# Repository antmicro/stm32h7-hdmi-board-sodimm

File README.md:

# SODIMM for STM32H7 HDMI Board

Copyright (c) 2026 [Antmicro](https://www.antmicro.com)

## Overview

This project includes PCB design files for a custom SDRAM memory module in SO-DIMM form factor. 
This module is compatible with [STM32H7 HDMI Board](https://github.com/antmicro/stm32h7-hdmi-board) developed by Antmicro. 
It provides 512 MB of SDRAM memory supporting a maximum memory clock frequency of 200 MHz, and exposes a 32-bit data bus for full compatibility with the STM32H747 FMC (Flexible Memory Controller) used in the STM32H7 HDMI Board design. 
The board design follows the JEDEC 144-pin SODIMM pin assignment with only half of the data bus implemented (32 bits).
It also features an EEPROM memory chip for Serial Presence Detect.
The board dimensions comply with the MO-190-C SODIMM Mechanical Specifications.
The PCB design files were prepared in KiCad 10.x.

## Key features

* 512 MB of SDRAM memory
* 144 Pin SODIMM PCB edge connector
* 2Rx8 (32 data bus) memory organization
* 8 x ISSI IS42S86400F-7TL SDRAM devices with a maximum clock frequency of 200MHz
* JEDEC 144-pin SODIMM pin-assignment with only half of the data bus implemented (DQ[0..31])
* Board outline compliant with the MO-190-C SODIMM Mechanical Specifications
* Compatible with STM32H747 FMC
* 67.6 x 31.75 mm (2.66 x 1.25 inch) PCB outline

## Project structure

The main directory contains KiCad PCB project files, the LICENSE, and this README, and the img directory contains graphics for this README.

## Licensing

This project is published under the [Apache-2.0](LICENSE) license.

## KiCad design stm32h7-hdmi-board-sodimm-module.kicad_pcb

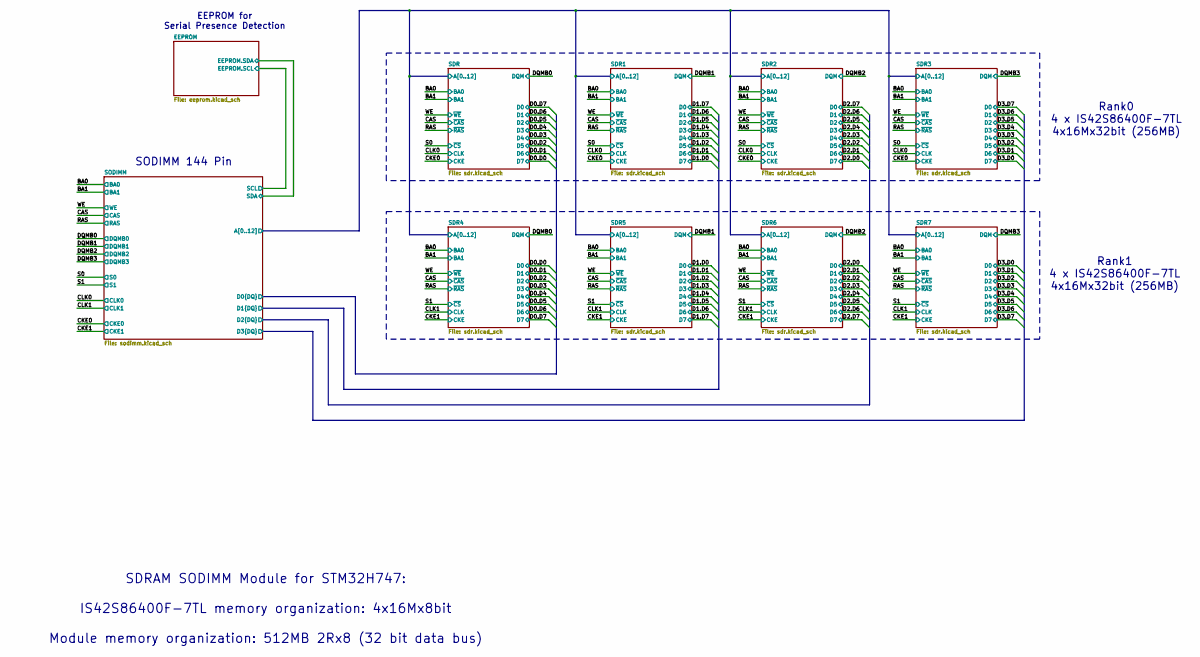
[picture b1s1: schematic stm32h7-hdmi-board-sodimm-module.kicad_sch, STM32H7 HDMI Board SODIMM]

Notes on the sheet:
Rank0 4 x IS42S86400F-7TL 4x16Mx32bit (256MB)
Rank1 4 x IS42S86400F-7TL 4x16Mx32bit (256MB)
SDRAM SODIMM Module for STM32H747: IS42S86400F-7TL memory organization: 4x16Mx8bit Module memory organization: 512MB 2Rx8 (32 bit data bus)
SODIMM 144 Pin
EEPROM for Serial Presence Detection

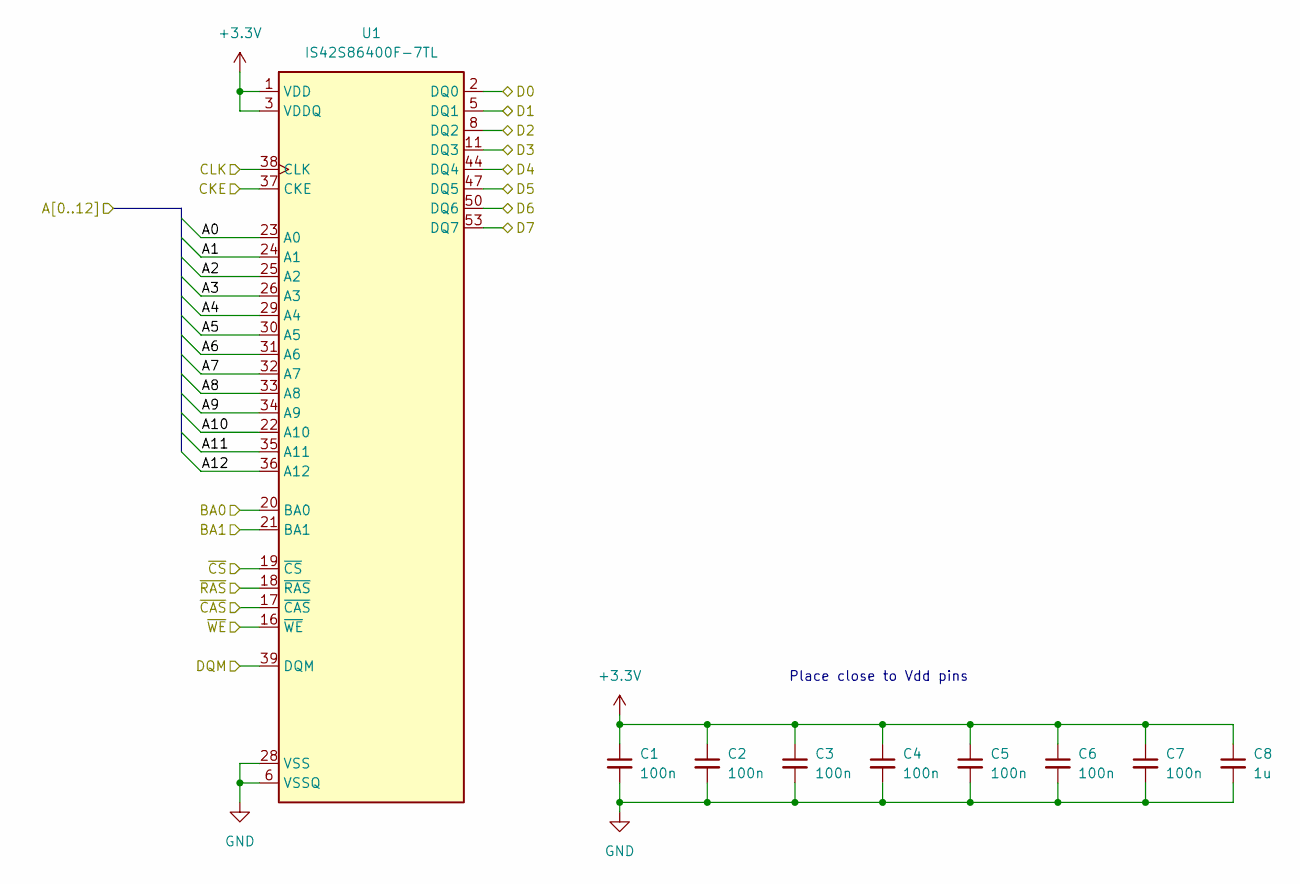
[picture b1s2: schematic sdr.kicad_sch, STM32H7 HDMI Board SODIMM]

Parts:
C1, C2, C3, C4, C5, C6, C7: C_100n_0402; C_0402_1005Metric; Voltage 50V; MPN GRM155R61H104KE14D
C8: C_1u_0402; C_0402_1005Metric; MPN C1005X6S1A105K050BC
U1: IS42S86400F-7TL; TSOP-II-54_22.2x10.16mm_P0.8mm; MPN IS42S86400F-7TL

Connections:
+3.3V: C1.1, C2.1, C3.1, C4.1, C5.1, C6.1, C7.1, C8.1, U1.1 (VDD), U1.3 (VDDQ), U1.9 (VDDQ), U1.14 (VDD), U1.27 (VDD), U1.43 (VDDQ), U1.49 (VDDQ); also elsewhere on the board
/BA0: U1.20 (BA0); also elsewhere on the board
/BA1: U1.21 (BA1); also elsewhere on the board
/CAS: U1.17 (~CAS); also elsewhere on the board
/CKE0: U1.37 (CKE); also elsewhere on the board
/CLK0: U1.38 (CLK); also elsewhere on the board
/DQMB0: U1.39 (DQM); also elsewhere on the board
/RAS: U1.18 (~RAS); also elsewhere on the board
/S0: U1.19 (~CS); also elsewhere on the board
/SDR/A0: U1.23 (A0); also elsewhere on the board
/SDR/A1: U1.24 (A1); also elsewhere on the board
/SDR/A2: U1.25 (A2); also elsewhere on the board
/SDR/A3: U1.26 (A3); also elsewhere on the board
/SDR/A4: U1.29 (A4); also elsewhere on the board
/SDR/A5: U1.30 (A5); also elsewhere on the board
/SDR/A6: U1.31 (A6); also elsewhere on the board
/SDR/A7: U1.32 (A7); also elsewhere on the board
/SDR/A8: U1.33 (A8); also elsewhere on the board
/SDR/A9: U1.34 (A9); also elsewhere on the board
/SDR/A10: U1.22 (A10); also elsewhere on the board
/SDR/A11: U1.35 (A11); also elsewhere on the board
/SDR/A12: U1.36 (A12); also elsewhere on the board
/SODIMM/D0.D0: U1.53 (DQ7); also elsewhere on the board
/SODIMM/D0.D1: U1.50 (DQ6); also elsewhere on the board
/SODIMM/D0.D2: U1.47 (DQ5); also elsewhere on the board
/SODIMM/D0.D3: U1.44 (DQ4); also elsewhere on the board
/SODIMM/D0.D4: U1.11 (DQ3); also elsewhere on the board
/SODIMM/D0.D5: U1.8 (DQ2); also elsewhere on the board
/SODIMM/D0.D6: U1.5 (DQ1); also elsewhere on the board
/SODIMM/D0.D7: U1.2 (DQ0); also elsewhere on the board
/WE: U1.16 (~WE); also elsewhere on the board
GND: C1.2, C2.2, C3.2, C4.2, C5.2, C6.2, C7.2, C8.2, U1.6 (VSSQ), U1.12 (VSSQ), U1.28 (VSS), U1.41 (VSS), U1.46 (VSSQ), U1.52 (VSSQ), U1.54 (VSS); also elsewhere on the board

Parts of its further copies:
C9, C10, C11, C12, C13, C14, C15, C17, C18, C19, C20, C21, C22, C23, C25, C26, C27, C28, C29, C30, C31, C33, C34, C35, C36, C37, C38, C39, C41, C42, C43, C44, C45, C46, C47, C49, C50, C51, C52, C53, C54, C55, C57, C58, C59, C60, C61, C62, C63: C_100n_0402; C_0402_1005Metric; Voltage 50V; MPN GRM155R61H104KE14D
C16, C24, C32, C40, C48, C56, C64: C_1u_0402; C_0402_1005Metric; MPN C1005X6S1A105K050BC
U2, U3, U4, U5, U6, U7, U8: IS42S86400F-7TL; TSOP-II-54_22.2x10.16mm_P0.8mm; MPN IS42S86400F-7TL

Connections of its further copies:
+3.3V: C9.1, C10.1, C11.1, C12.1, C13.1, C14.1, C15.1, C16.1, C17.1, C18.1, C19.1, C20.1, C21.1, C22.1, C23.1, C24.1, C25.1, C26.1, C27.1, C28.1, C29.1, C30.1, C31.1, C32.1, C33.1, C34.1, C35.1, C36.1, C37.1, C38.1, C39.1, C40.1, C41.1, C42.1, C43.1, C44.1, C45.1, C46.1, C47.1, C48.1, C49.1, C50.1, C51.1, C52.1, C53.1, C54.1, C55.1, C56.1, C57.1, C58.1, C59.1, C60.1, C61.1, C62.1, C63.1, C64.1, U2.1 (VDD), U2.3 (VDDQ), U2.9 (VDDQ), U2.14 (VDD), U2.27 (VDD), U2.43 (VDDQ), U2.49 (VDDQ), U3.1 (VDD), U3.3 (VDDQ), U3.9 (VDDQ), U3.14 (VDD), U3.27 (VDD), U3.43 (VDDQ), U3.49 (VDDQ), U4.1 (VDD), U4.3 (VDDQ), U4.9 (VDDQ), U4.14 (VDD), U4.27 (VDD), U4.43 (VDDQ), U4.49 (VDDQ), U5.1 (VDD), U5.3 (VDDQ), U5.9 (VDDQ), U5.14 (VDD), U5.27 (VDD), U5.43 (VDDQ), U5.49 (VDDQ), U6.1 (VDD), U6.3 (VDDQ), U6.9 (VDDQ), U6.14 (VDD), U6.27 (VDD), U6.43 (VDDQ), U6.49 (VDDQ), U7.1 (VDD), U7.3 (VDDQ), U7.9 (VDDQ), U7.14 (VDD), U7.27 (VDD), U7.43 (VDDQ), U7.49 (VDDQ), U8.1 (VDD), U8.3 (VDDQ), U8.9 (VDDQ), U8.14 (VDD), U8.27 (VDD), U8.43 (VDDQ), U8.49 (VDDQ); also elsewhere on the board
/BA0: U2.20 (BA0), U3.20 (BA0), U4.20 (BA0), U5.20 (BA0), U6.20 (BA0), U7.20 (BA0), U8.20 (BA0); also elsewhere on the board
/BA1: U2.21 (BA1), U3.21 (BA1), U4.21 (BA1), U5.21 (BA1), U6.21 (BA1), U7.21 (BA1), U8.21 (BA1); also elsewhere on the board
/CAS: U2.17 (~CAS), U3.17 (~CAS), U4.17 (~CAS), U5.17 (~CAS), U6.17 (~CAS), U7.17 (~CAS), U8.17 (~CAS); also elsewhere on the board
/CKE0: U2.37 (CKE), U3.37 (CKE), U4.37 (CKE); also elsewhere on the board
/CKE1: U5.37 (CKE), U6.37 (CKE), U7.37 (CKE), U8.37 (CKE); also elsewhere on the board
/CLK0: U2.38 (CLK), U3.38 (CLK), U4.38 (CLK); also elsewhere on the board
/CLK1: U5.38 (CLK), U6.38 (CLK), U7.38 (CLK), U8.38 (CLK); also elsewhere on the board
/DQMB0: U5.39 (DQM); also elsewhere on the board
/DQMB1: U2.39 (DQM), U6.39 (DQM); also elsewhere on the board
/DQMB2: U3.39 (DQM), U7.39 (DQM); also elsewhere on the board
/DQMB3: U4.39 (DQM), U8.39 (DQM); also elsewhere on the board
/RAS: U2.18 (~RAS), U3.18 (~RAS), U4.18 (~RAS), U5.18 (~RAS), U6.18 (~RAS), U7.18 (~RAS), U8.18 (~RAS); also elsewhere on the board
/S0: U2.19 (~CS), U3.19 (~CS), U4.19 (~CS); also elsewhere on the board
/S1: U5.19 (~CS), U6.19 (~CS), U7.19 (~CS), U8.19 (~CS); also elsewhere on the board
/SDR/A0: U2.23 (A0), U3.23 (A0), U4.23 (A0), U5.23 (A0), U6.23 (A0), U7.23 (A0), U8.23 (A0); also elsewhere on the board
/SDR/A1: U2.24 (A1), U3.24 (A1), U4.24 (A1), U5.24 (A1), U6.24 (A1), U7.24 (A1), U8.24 (A1); also elsewhere on the board
/SDR/A2: U2.25 (A2), U3.25 (A2), U4.25 (A2), U5.25 (A2), U6.25 (A2), U7.25 (A2), U8.25 (A2); also elsewhere on the board
/SDR/A3: U2.26 (A3), U3.26 (A3), U4.26 (A3), U5.26 (A3), U6.26 (A3), U7.26 (A3), U8.26 (A3); also elsewhere on the board
/SDR/A4: U2.29 (A4), U3.29 (A4), U4.29 (A4), U5.29 (A4), U6.29 (A4), U7.29 (A4), U8.29 (A4); also elsewhere on the board
/SDR/A5: U2.30 (A5), U3.30 (A5), U4.30 (A5), U5.30 (A5), U6.30 (A5), U7.30 (A5), U8.30 (A5); also elsewhere on the board
/SDR/A6: U2.31 (A6), U3.31 (A6), U4.31 (A6), U5.31 (A6), U6.31 (A6), U7.31 (A6), U8.31 (A6); also elsewhere on the board
/SDR/A7: U2.32 (A7), U3.32 (A7), U4.32 (A7), U5.32 (A7), U6.32 (A7), U7.32 (A7), U8.32 (A7); also elsewhere on the board
/SDR/A8: U2.33 (A8), U3.33 (A8), U4.33 (A8), U5.33 (A8), U6.33 (A8), U7.33 (A8), U8.33 (A8); also elsewhere on the board
/SDR/A9: U2.34 (A9), U3.34 (A9), U4.34 (A9), U5.34 (A9), U6.34 (A9), U7.34 (A9), U8.34 (A9); also elsewhere on the board
/SDR/A10: U2.22 (A10), U3.22 (A10), U4.22 (A10), U5.22 (A10), U6.22 (A10), U7.22 (A10), U8.22 (A10); also elsewhere on the board
/SDR/A11: U2.35 (A11), U3.35 (A11), U4.35 (A11), U5.35 (A11), U6.35 (A11), U7.35 (A11), U8.35 (A11); also elsewhere on the board
/SDR/A12: U2.36 (A12), U3.36 (A12), U4.36 (A12), U5.36 (A12), U6.36 (A12), U7.36 (A12), U8.36 (A12); also elsewhere on the board
/SODIMM/D0.D0: U5.2 (DQ0); also elsewhere on the board
/SODIMM/D0.D1: U5.5 (DQ1); also elsewhere on the board
/SODIMM/D0.D2: U5.8 (DQ2); also elsewhere on the board
/SODIMM/D0.D3: U5.11 (DQ3); also elsewhere on the board
/SODIMM/D0.D4: U5.44 (DQ4); also elsewhere on the board
/SODIMM/D0.D5: U5.47 (DQ5); also elsewhere on the board
/SODIMM/D0.D6: U5.50 (DQ6); also elsewhere on the board
/SODIMM/D0.D7: U5.53 (DQ7); also elsewhere on the board
/SODIMM/D1.D0: U2.53 (DQ7), U6.2 (DQ0); also elsewhere on the board
/SODIMM/D1.D1: U2.50 (DQ6), U6.5 (DQ1); also elsewhere on the board
/SODIMM/D1.D2: U2.47 (DQ5), U6.8 (DQ2); also elsewhere on the board
/SODIMM/D1.D3: U2.44 (DQ4), U6.11 (DQ3); also elsewhere on the board
/SODIMM/D1.D4: U2.11 (DQ3), U6.44 (DQ4); also elsewhere on the board
/SODIMM/D1.D5: U2.8 (DQ2), U6.47 (DQ5); also elsewhere on the board
/SODIMM/D1.D6: U2.5 (DQ1), U6.50 (DQ6); also elsewhere on the board
/SODIMM/D1.D7: U2.2 (DQ0), U6.53 (DQ7); also elsewhere on the board
/SODIMM/D2.D0: U3.53 (DQ7), U7.2 (DQ0); also elsewhere on the board
/SODIMM/D2.D1: U3.50 (DQ6), U7.5 (DQ1); also elsewhere on the board
/SODIMM/D2.D2: U3.47 (DQ5), U7.8 (DQ2); also elsewhere on the board
/SODIMM/D2.D3: U3.44 (DQ4), U7.11 (DQ3); also elsewhere on the board
/SODIMM/D2.D4: U3.11 (DQ3), U7.44 (DQ4); also elsewhere on the board
/SODIMM/D2.D5: U3.8 (DQ2), U7.47 (DQ5); also elsewhere on the board
/SODIMM/D2.D6: U3.5 (DQ1), U7.50 (DQ6); also elsewhere on the board
/SODIMM/D2.D7: U3.2 (DQ0), U7.53 (DQ7); also elsewhere on the board
/SODIMM/D3.D0: U4.53 (DQ7), U8.2 (DQ0); also elsewhere on the board
/SODIMM/D3.D1: U4.50 (DQ6), U8.5 (DQ1); also elsewhere on the board
/SODIMM/D3.D2: U4.47 (DQ5), U8.8 (DQ2); also elsewhere on the board
/SODIMM/D3.D3: U4.44 (DQ4), U8.11 (DQ3); also elsewhere on the board
/SODIMM/D3.D4: U4.11 (DQ3), U8.44 (DQ4); also elsewhere on the board
/SODIMM/D3.D5: U4.8 (DQ2), U8.47 (DQ5); also elsewhere on the board
/SODIMM/D3.D6: U4.5 (DQ1), U8.50 (DQ6); also elsewhere on the board
/SODIMM/D3.D7: U4.2 (DQ0), U8.53 (DQ7); also elsewhere on the board
/WE: U2.16 (~WE), U3.16 (~WE), U4.16 (~WE), U5.16 (~WE), U6.16 (~WE), U7.16 (~WE), U8.16 (~WE); also elsewhere on the board
GND: C9.2, C10.2, C11.2, C12.2, C13.2, C14.2, C15.2, C16.2, C17.2, C18.2, C19.2, C20.2, C21.2, C22.2, C23.2, C24.2, C25.2, C26.2, C27.2, C28.2, C29.2, C30.2, C31.2, C32.2, C33.2, C34.2, C35.2, C36.2, C37.2, C38.2, C39.2, C40.2, C41.2, C42.2, C43.2, C44.2, C45.2, C46.2, C47.2, C48.2, C49.2, C50.2, C51.2, C52.2, C53.2, C54.2, C55.2, C56.2, C57.2, C58.2, C59.2, C60.2, C61.2, C62.2, C63.2, C64.2, U2.6 (VSSQ), U2.12 (VSSQ), U2.28 (VSS), U2.41 (VSS), U2.46 (VSSQ), U2.52 (VSSQ), U2.54 (VSS), U3.6 (VSSQ), U3.12 (VSSQ), U3.28 (VSS), U3.41 (VSS), U3.46 (VSSQ), U3.52 (VSSQ), U3.54 (VSS), U4.6 (VSSQ), U4.12 (VSSQ), U4.28 (VSS), U4.41 (VSS), U4.46 (VSSQ), U4.52 (VSSQ), U4.54 (VSS), U5.6 (VSSQ), U5.12 (VSSQ), U5.28 (VSS), U5.41 (VSS), U5.46 (VSSQ), U5.52 (VSSQ), U5.54 (VSS), U6.6 (VSSQ), U6.12 (VSSQ), U6.28 (VSS), U6.41 (VSS), U6.46 (VSSQ), U6.52 (VSSQ), U6.54 (VSS), U7.6 (VSSQ), U7.12 (VSSQ), U7.28 (VSS), U7.41 (VSS), U7.46 (VSSQ), U7.52 (VSSQ), U7.54 (VSS), U8.6 (VSSQ), U8.12 (VSSQ), U8.28 (VSS), U8.41 (VSS), U8.46 (VSSQ), U8.52 (VSSQ), U8.54 (VSS); also elsewhere on the board

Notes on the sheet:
Place close to Vdd pins

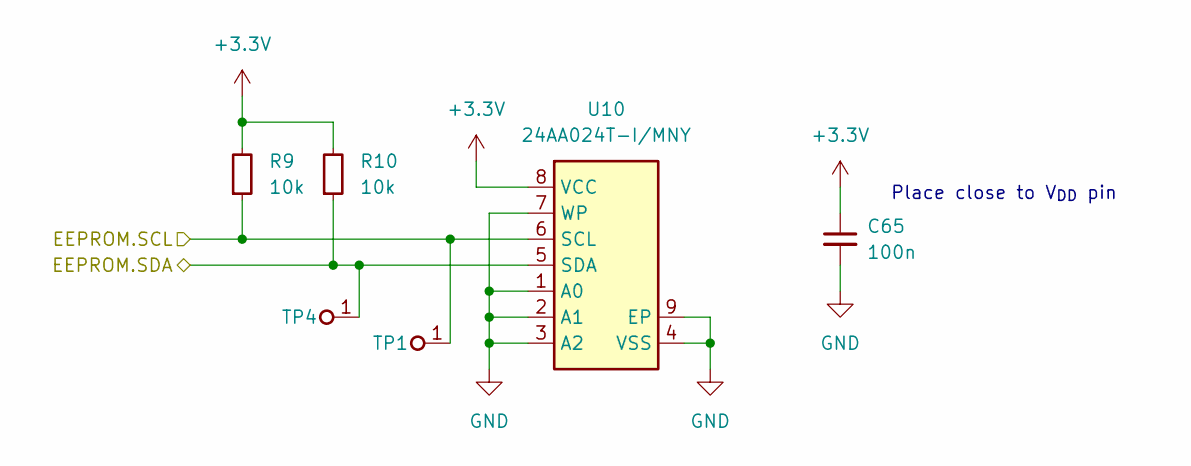
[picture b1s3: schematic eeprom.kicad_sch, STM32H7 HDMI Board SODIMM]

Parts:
C65: C_100n_0402; C_0402_1005Metric; Voltage 50V; MPN GRM155R61H104KE14D
R9, R10: R_10k_0402; R_0402_1005Metric; Tolerance 1%; MPN CR0402-FX-1002GLF
TP1, TP4: TP_1mm_SMD; TP_SMD_1mm
U10: 24AA024_TDFN; TDFN-8-1EP_2x3x0.8mm_P0.5mm_EP1.3x1.4mm; MPN 24AA024T-I/MNY

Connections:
+3.3V: C65.1, R9.2, R10.2, U10.8 (VCC); also elsewhere on the board
/EEPROM/EEPROM.SCL: R9.1, TP1.1 (1_1), U10.6 (SCL); also elsewhere on the board
/EEPROM/EEPROM.SDA: R10.1, TP4.1 (1_1), U10.5 (SDA); also elsewhere on the board
GND: C65.2, U10.1 (A0), U10.2 (A1), U10.3 (A2), U10.4 (VSS), U10.7 (WP), U10.9 (EP); also elsewhere on the board

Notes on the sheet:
Place close to V_{DD} pin

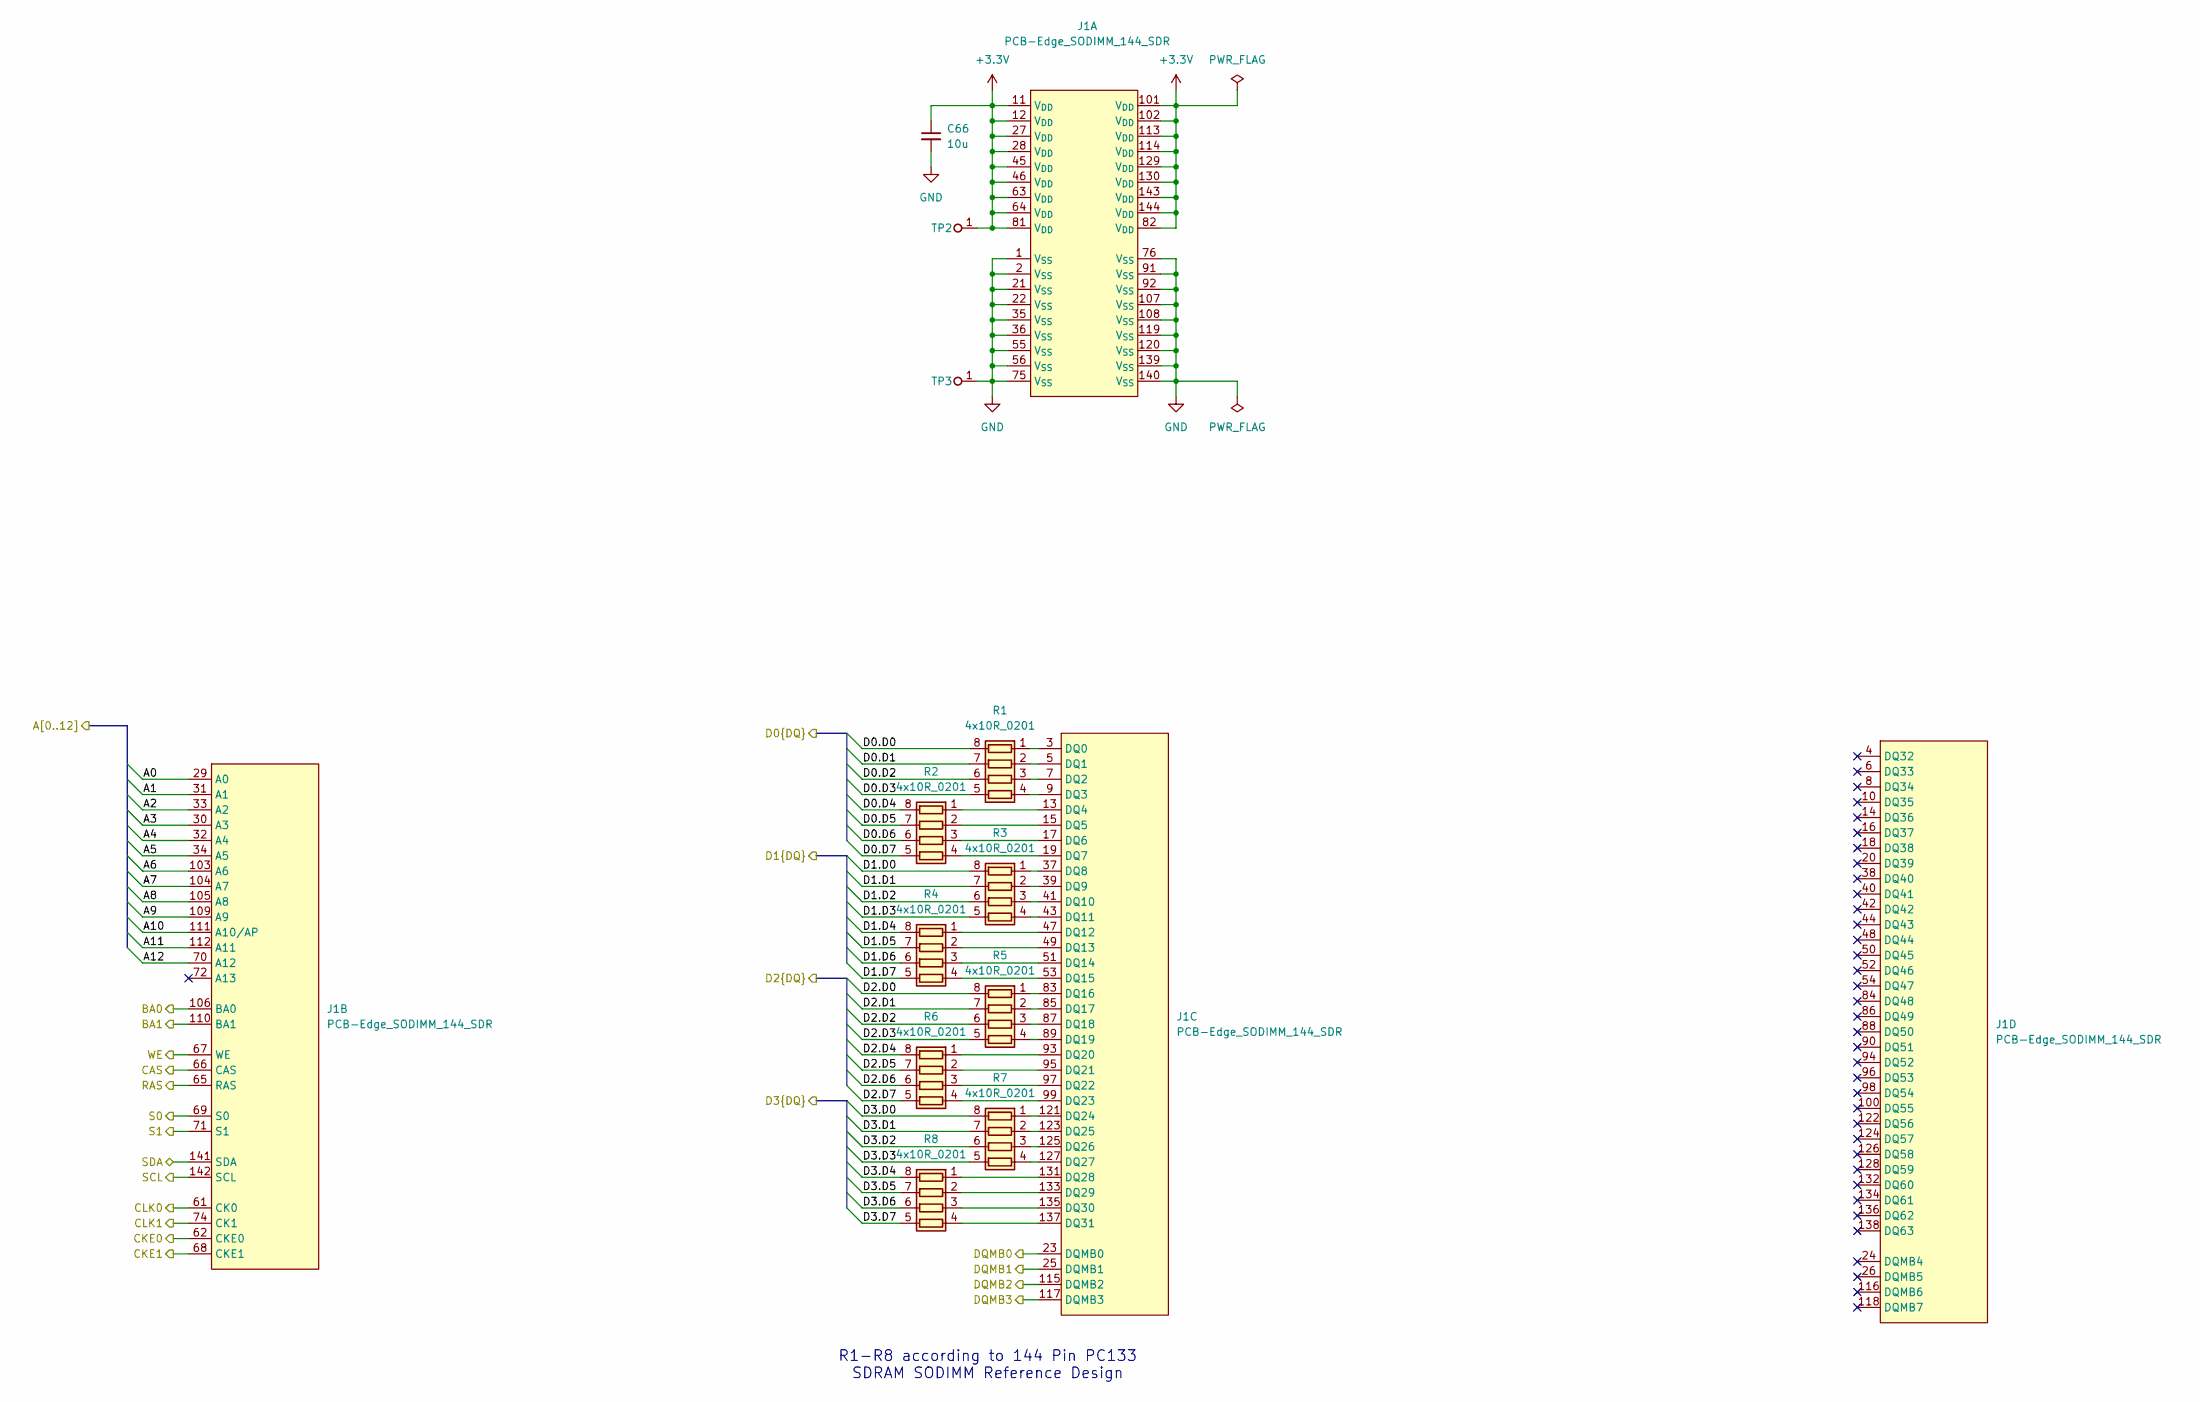
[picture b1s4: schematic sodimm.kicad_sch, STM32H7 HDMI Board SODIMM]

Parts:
C66: C_10u_0402; C_0402_1005Metric; MPN CC0402MRX5R5BB106
J1: PCB-Edge_SODIMM_144_SDR
R1, R2, R3, R4, R5, R6, R7, R8: 4x10R_0201_array; R_Array_4x0201_Panasonic_EXB18V; MPN EXB-18V100JX
TP2, TP3: TP_1mm_SMD; TP_SMD_1mm

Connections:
+3.3V: C66.1, J1.11 (V_{DD}), J1.12 (V_{DD}), J1.27 (V_{DD}), J1.28 (V_{DD}), J1.45 (V_{DD}), J1.46 (V_{DD}), J1.63 (V_{DD}), J1.64 (V_{DD}), J1.81 (V_{DD}), J1.82 (V_{DD}), J1.101 (V_{DD}), J1.102 (V_{DD}), J1.113 (V_{DD}), J1.114 (V_{DD}), J1.129 (V_{DD}), J1.130 (V_{DD}), J1.143 (V_{DD}), J1.144 (V_{DD}), TP2.1 (1_1); also elsewhere on the board
/BA0: J1.106 (BA0); also elsewhere on the board
/BA1: J1.110 (BA1); also elsewhere on the board
/CAS: J1.66 (CAS); also elsewhere on the board
/CKE0: J1.62 (CKE0); also elsewhere on the board
/CKE1: J1.68 (CKE1); also elsewhere on the board
/CLK0: J1.61 (CK0); also elsewhere on the board
/CLK1: J1.74 (CK1); also elsewhere on the board
/DQMB0: J1.23 (DQMB0); also elsewhere on the board
/DQMB1: J1.25 (DQMB1); also elsewhere on the board
/DQMB2: J1.115 (DQMB2); also elsewhere on the board
/DQMB3: J1.117 (DQMB3); also elsewhere on the board
/EEPROM/EEPROM.SCL: J1.142 (SCL); also elsewhere on the board
/EEPROM/EEPROM.SDA: J1.141 (SDA); also elsewhere on the board
/RAS: J1.65 (RAS); also elsewhere on the board
/S0: J1.69 (S0); also elsewhere on the board
/S1: J1.71 (S1); also elsewhere on the board
/SDR/A0: J1.29 (A0); also elsewhere on the board
/SDR/A1: J1.31 (A1); also elsewhere on the board
/SDR/A2: J1.33 (A2); also elsewhere on the board
/SDR/A3: J1.30 (A3); also elsewhere on the board
/SDR/A4: J1.32 (A4); also elsewhere on the board
/SDR/A5: J1.34 (A5); also elsewhere on the board
/SDR/A6: J1.103 (A6); also elsewhere on the board
/SDR/A7: J1.104 (A7); also elsewhere on the board
/SDR/A8: J1.105 (A8); also elsewhere on the board
/SDR/A9: J1.109 (A9); also elsewhere on the board
/SDR/A10: J1.111 (A10/AP); also elsewhere on the board
/SDR/A11: J1.112 (A11); also elsewhere on the board
/SDR/A12: J1.70 (A12); also elsewhere on the board
/SODIMM/D0.D0: R1.8 (R1.2); also elsewhere on the board
/SODIMM/D0.D1: R1.7 (R2.2); also elsewhere on the board
/SODIMM/D0.D2: R1.6 (R3.2); also elsewhere on the board
/SODIMM/D0.D3: R1.5 (R4.2); also elsewhere on the board
/SODIMM/D0.D4: R2.8 (R1.2); also elsewhere on the board
/SODIMM/D0.D5: R2.7 (R2.2); also elsewhere on the board
/SODIMM/D0.D6: R2.6 (R3.2); also elsewhere on the board
/SODIMM/D0.D7: R2.5 (R4.2); also elsewhere on the board
/SODIMM/D1.D0: R3.8 (R1.2); also elsewhere on the board
/SODIMM/D1.D1: R3.7 (R2.2); also elsewhere on the board
/SODIMM/D1.D2: R3.6 (R3.2); also elsewhere on the board
/SODIMM/D1.D3: R3.5 (R4.2); also elsewhere on the board
/SODIMM/D1.D4: R4.8 (R1.2); also elsewhere on the board
/SODIMM/D1.D5: R4.7 (R2.2); also elsewhere on the board
/SODIMM/D1.D6: R4.6 (R3.2); also elsewhere on the board
/SODIMM/D1.D7: R4.5 (R4.2); also elsewhere on the board
/SODIMM/D2.D0: R5.8 (R1.2); also elsewhere on the board
/SODIMM/D2.D1: R5.7 (R2.2); also elsewhere on the board
/SODIMM/D2.D2: R5.6 (R3.2); also elsewhere on the board
/SODIMM/D2.D3: R5.5 (R4.2); also elsewhere on the board
/SODIMM/D2.D4: R6.8 (R1.2); also elsewhere on the board
/SODIMM/D2.D5: R6.7 (R2.2); also elsewhere on the board
/SODIMM/D2.D6: R6.6 (R3.2); also elsewhere on the board
/SODIMM/D2.D7: R6.5 (R4.2); also elsewhere on the board
/SODIMM/D3.D0: R7.8 (R1.2); also elsewhere on the board
/SODIMM/D3.D1: R7.7 (R2.2); also elsewhere on the board
/SODIMM/D3.D2: R7.6 (R3.2); also elsewhere on the board
/SODIMM/D3.D3: R7.5 (R4.2); also elsewhere on the board
/SODIMM/D3.D4: R8.8 (R1.2); also elsewhere on the board
/SODIMM/D3.D5: R8.7 (R2.2); also elsewhere on the board
/SODIMM/D3.D6: R8.6 (R3.2); also elsewhere on the board
/SODIMM/D3.D7: R8.5 (R4.2); also elsewhere on the board
/WE: J1.67 (WE); also elsewhere on the board
GND: C66.2, J1.1 (V_{SS}), J1.2 (V_{SS}), J1.21 (V_{SS}), J1.22 (V_{SS}), J1.35 (V_{SS}), J1.36 (V_{SS}), J1.55 (V_{SS}), J1.56 (V_{SS}), J1.75 (V_{SS}), J1.76 (V_{SS}), J1.91 (V_{SS}), J1.92 (V_{SS}), J1.107 (V_{SS}), J1.108 (V_{SS}), J1.119 (V_{SS}), J1.120 (V_{SS}), J1.139 (V_{SS}), J1.140 (V_{SS}), TP3.1 (1_1); also elsewhere on the board
unnamed: J1.3 (DQ0), R1.1 (R1.1)
unnamed: J1.5 (DQ1), R1.2 (R2.1)
unnamed: J1.7 (DQ2), R1.3 (R3.1)
unnamed: J1.9 (DQ3), R1.4 (R4.1)
unnamed: J1.13 (DQ4), R2.1 (R1.1)
unnamed: J1.15 (DQ5), R2.2 (R2.1)
unnamed: J1.17 (DQ6), R2.3 (R3.1)
unnamed: J1.19 (DQ7), R2.4 (R4.1)
unnamed: J1.37 (DQ8), R3.1 (R1.1)
unnamed: J1.39 (DQ9), R3.2 (R2.1)
unnamed: J1.41 (DQ10), R3.3 (R3.1)
unnamed: J1.43 (DQ11), R3.4 (R4.1)
unnamed: J1.47 (DQ12), R4.1 (R1.1)
unnamed: J1.49 (DQ13), R4.2 (R2.1)
unnamed: J1.51 (DQ14), R4.3 (R3.1)
unnamed: J1.53 (DQ15), R4.4 (R4.1)
unnamed: J1.83 (DQ16), R5.1 (R1.1)
unnamed: J1.85 (DQ17), R5.2 (R2.1)
unnamed: J1.87 (DQ18), R5.3 (R3.1)
unnamed: J1.89 (DQ19), R5.4 (R4.1)
unnamed: J1.93 (DQ20), R6.1 (R1.1)
unnamed: J1.95 (DQ21), R6.2 (R2.1)
unnamed: J1.97 (DQ22), R6.3 (R3.1)
unnamed: J1.99 (DQ23), R6.4 (R4.1)
unnamed: J1.121 (DQ24), R7.1 (R1.1)
unnamed: J1.123 (DQ25), R7.2 (R2.1)
unnamed: J1.125 (DQ26), R7.3 (R3.1)
unnamed: J1.127 (DQ27), R7.4 (R4.1)
unnamed: J1.131 (DQ28), R8.1 (R1.1)
unnamed: J1.133 (DQ29), R8.2 (R2.1)
unnamed: J1.135 (DQ30), R8.3 (R3.1)
unnamed: J1.137 (DQ31), R8.4 (R4.1)

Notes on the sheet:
R1-R8 according to 144 Pin PC133 SDRAM SODIMM Reference Design

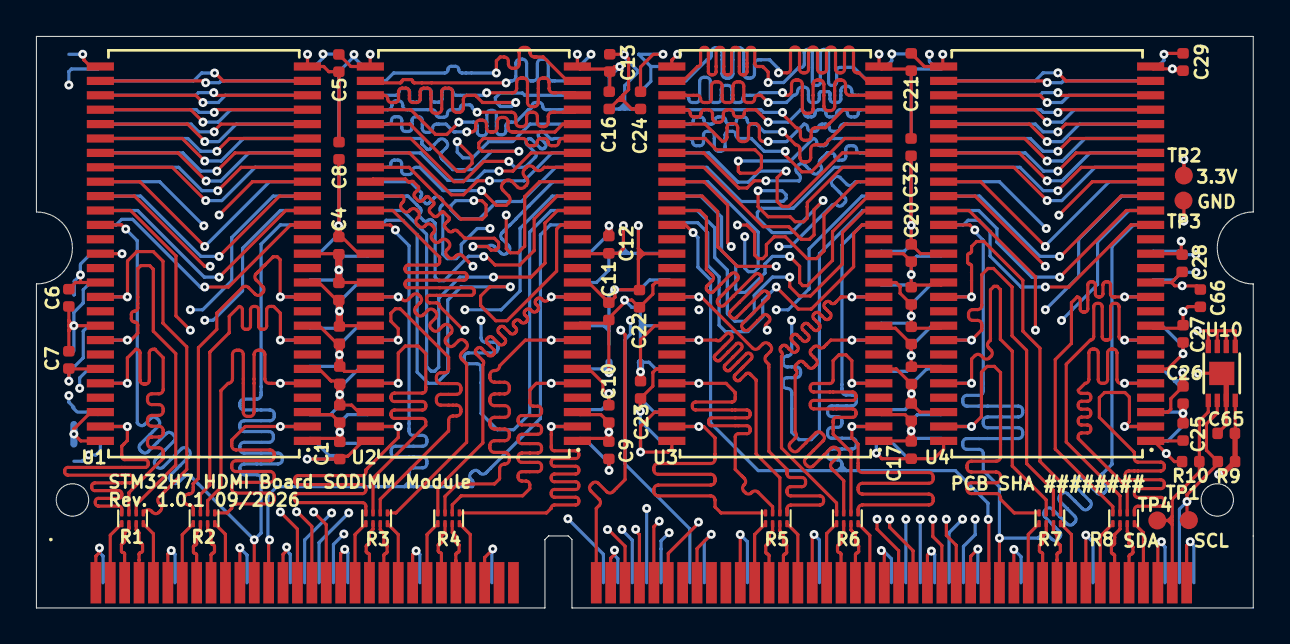
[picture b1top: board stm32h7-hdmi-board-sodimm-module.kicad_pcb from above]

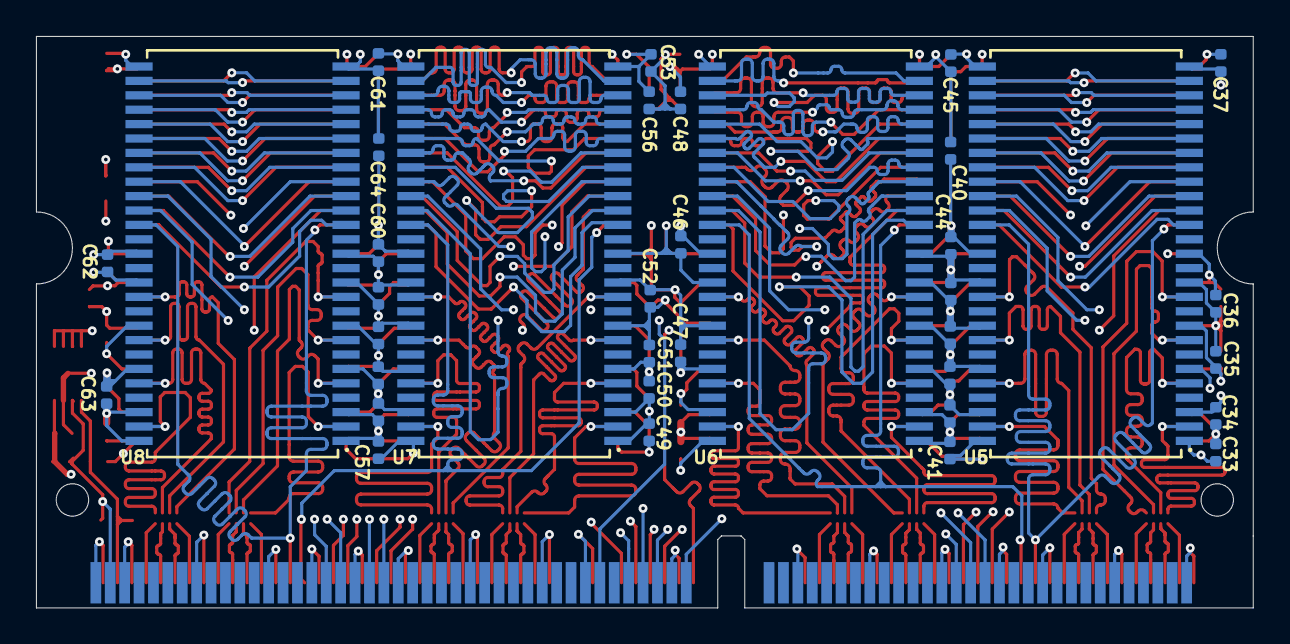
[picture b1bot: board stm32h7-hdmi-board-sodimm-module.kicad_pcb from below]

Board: 6 copper layers, 67.6 x 31.8 mm, 90 parts (36 on the bottom side), 96 nets.

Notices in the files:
parts and their libraries:
License: Apache-2.0
